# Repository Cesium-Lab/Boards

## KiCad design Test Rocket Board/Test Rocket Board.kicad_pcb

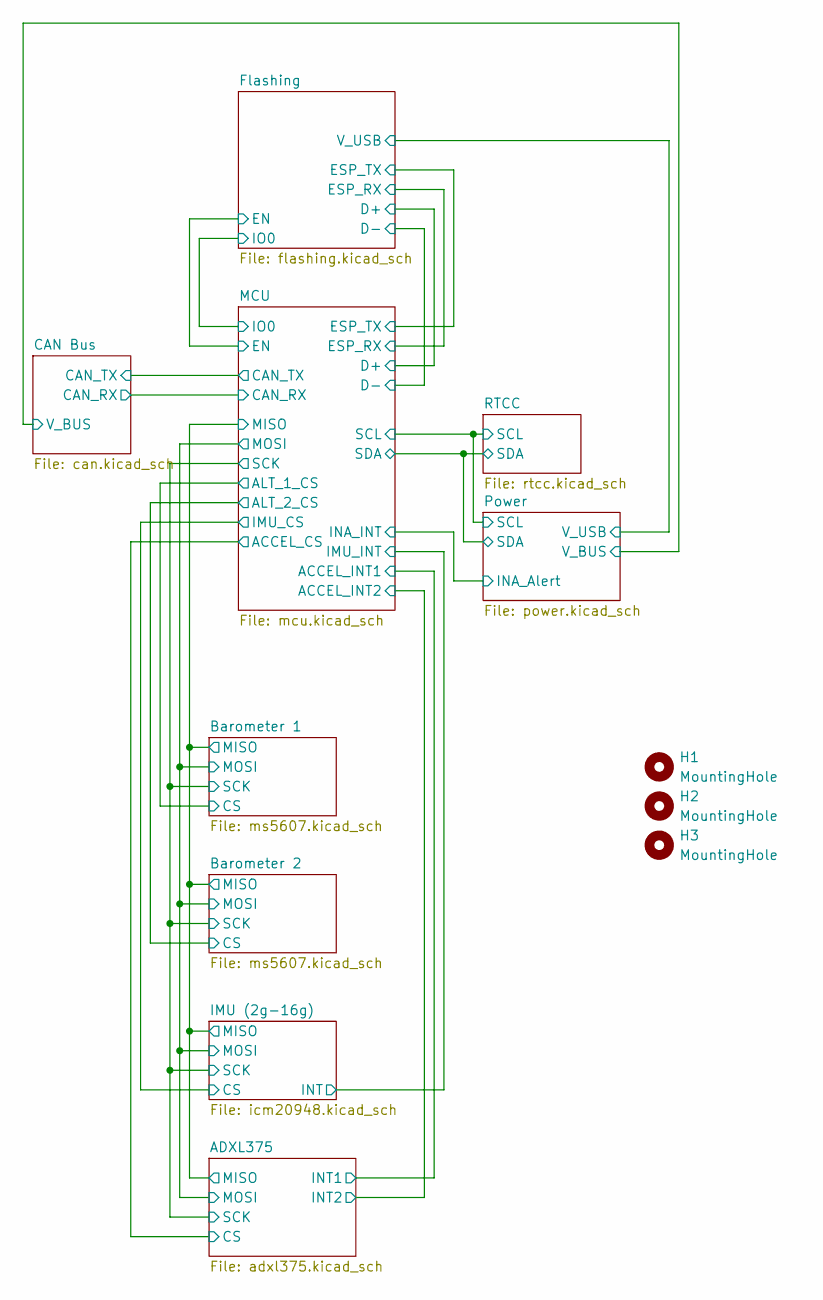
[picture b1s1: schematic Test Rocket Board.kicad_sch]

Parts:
H1, H2, H3: MountingHole; MountingHole_3.2mm_M3

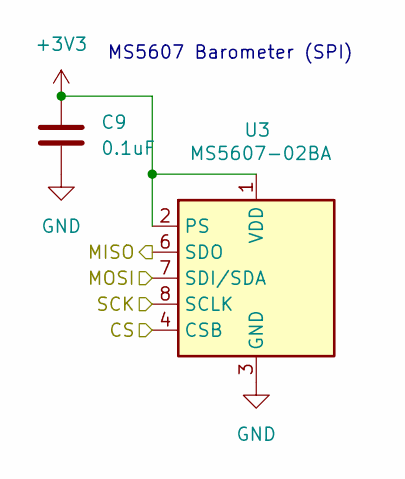
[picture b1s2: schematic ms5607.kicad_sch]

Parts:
C9: 0.1uF; C_0603_1608Metric
U3: MS5607-02BA; LGA-8_3x5mm_P1.25mm

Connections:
+3V3: C9.1, U3.1 (VDD), U3.2 (PS); also elsewhere on the board
/ADXL375/MISO: U3.6 (SDO); also elsewhere on the board
/ADXL375/MOSI: U3.7 (SDI/SDA); also elsewhere on the board
/ADXL375/SCK: U3.8 (SCLK); also elsewhere on the board
/Barometer 1/CS: U3.4 (CSB), U3.5 (CSB); also elsewhere on the board
GND: C9.2, U3.3 (GND); also elsewhere on the board

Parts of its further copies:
C10: 0.1uF; C_0603_1608Metric
U4: MS5607-02BA; LGA-8_3x5mm_P1.25mm

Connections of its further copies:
+3V3: C10.1, U4.1 (VDD), U4.2 (PS); also elsewhere on the board
/ADXL375/MISO: U4.6 (SDO); also elsewhere on the board
/ADXL375/MOSI: U4.7 (SDI/SDA); also elsewhere on the board
/ADXL375/SCK: U4.8 (SCLK); also elsewhere on the board
/Barometer 2/CS: U4.4 (CSB), U4.5 (CSB); also elsewhere on the board
GND: C10.2, U4.3 (GND); also elsewhere on the board

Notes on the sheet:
MS5607 Barometer (SPI)

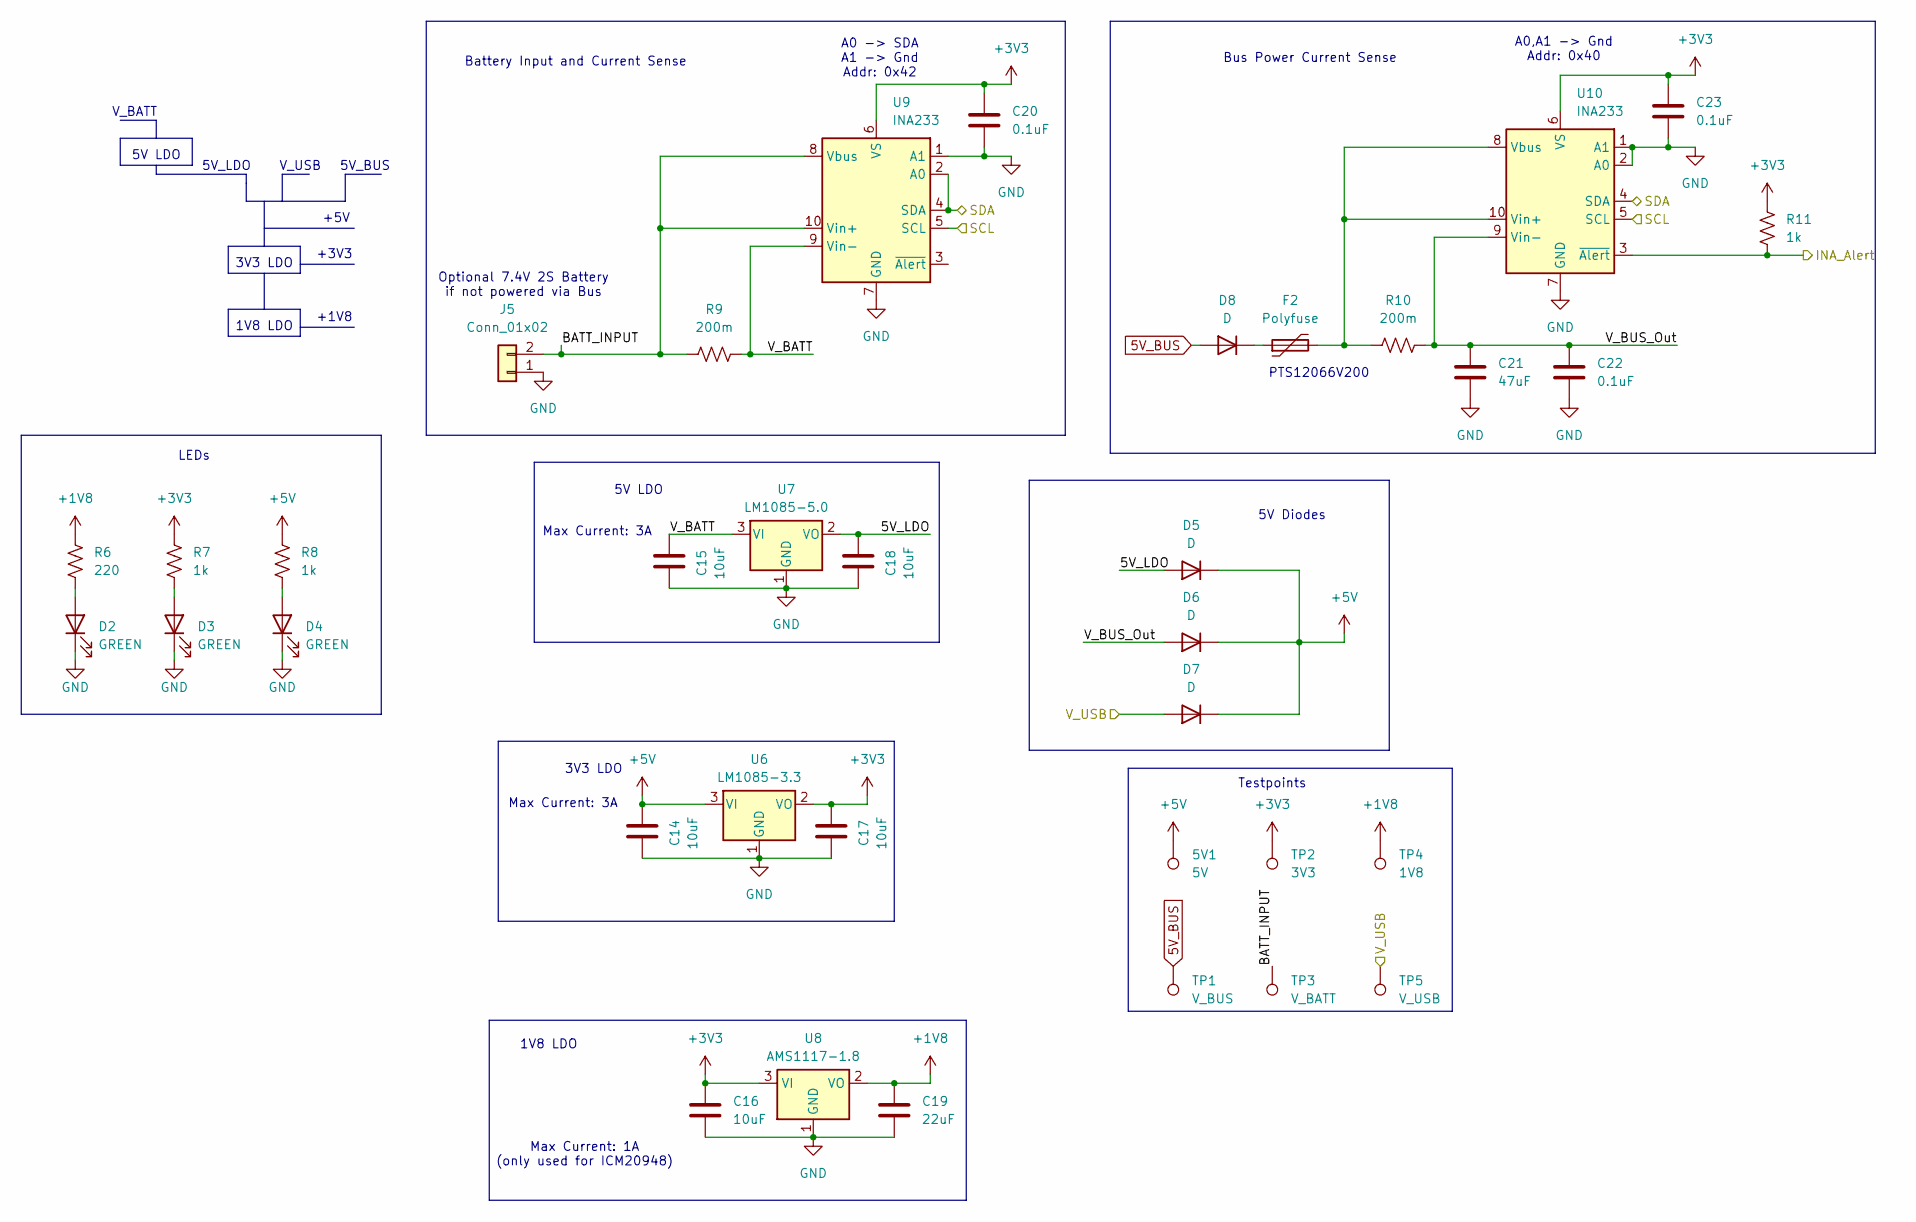
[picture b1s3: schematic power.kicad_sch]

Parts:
5V1: 5V; PinHeader_1x01_P2.54mm_Vertical
C14, C15, C16, C17, C18: 10uF; C_0603_1608Metric
C19: 22uF; C_0603_1608Metric
C20, C22, C23: 0.1uF; C_0603_1608Metric
C21: 47uF; C_0603_1608Metric
D2, D3, D4: GREEN; LED_0603_1608Metric_Pad1.05x0.95mm_HandSolder
D5, D6, D7, D8: D; D_0603_1608Metric
F2: Polyfuse; Fuse_1206_3216Metric
J5: Conn_01x02; AMASS_XT60-M_1x02_P7.20mm_Vertical
R6: 220; R_0603_1608Metric
R7, R8, R11: 1k; R_0603_1608Metric
R9, R10: 200m; R_0603_1608Metric
TP1: V_BUS; PinHeader_1x01_P2.54mm_Vertical
TP2: 3V3; PinHeader_1x01_P2.54mm_Vertical
TP3: V_BATT; PinHeader_1x01_P2.54mm_Vertical
TP4: 1V8; PinHeader_1x01_P2.54mm_Vertical
TP5: V_USB; PinHeader_1x01_P2.54mm_Vertical
U6: LM1085-3.3; TO-263-3_TabPin2
U7: LM1085-5.0; TO-263-3_TabPin2
U8: AMS1117-1.8; SOT-223-3_TabPin2
U9, U10: INA233; VSSOP-10_3x3mm_P0.5mm

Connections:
5V_BUS: D8.2 (A), TP1.1; also elsewhere on the board
+1V8: C19.1, R6.2, TP4.1, U8.2 (VO); also elsewhere on the board
+3V3: C16.1, C17.2, C20.1, C23.1, R7.2, R11.2, TP2.1, U6.2 (VO), U8.3 (VI), U9.6 (VS), U10.6 (VS); also elsewhere on the board
+5V: 5V1.1, C14.2, D5.1 (K), D6.1 (K), D7.1 (K), R8.2, U6.3 (VI); also elsewhere on the board
/Flashing/V_USB: D7.2 (A), TP5.1; also elsewhere on the board
/MCU/INA_INT: R11.1, U10.3 (~Alert); also elsewhere on the board
/MCU/SCL: U9.5 (SCL), U10.5 (SCL); also elsewhere on the board
/MCU/SDA: U9.2 (A0), U9.4 (SDA), U10.4 (SDA); also elsewhere on the board
/Power/5V_LDO: C18.2, D5.2 (A), U7.2 (VO)
/Power/BATT_INPUT: J5.2, R9.1, TP3.1, U9.8 (Vbus), U9.10 (Vin+)
/Power/V_BATT: C15.2, R9.2, U7.3 (VI), U9.9 (Vin-)
/Power/V_BUS_Out: C21.1, C22.1, D6.2 (A), R10.2, U10.9 (Vin-)
GND: C14.1, C15.1, C16.2, C17.1, C18.1, C19.2, C20.2, C21.2, C22.2, C23.2, D2.1 (K), D3.1 (K), D4.1 (K), J5.1, U6.1 (GND), U7.1 (GND), U8.1 (GND), U9.1 (A1), U9.7 (GND), U10.1 (A1), U10.2 (A0), U10.7 (GND); also elsewhere on the board
unnamed: D2.2 (A), R6.1
unnamed: D3.2 (A), R7.1
unnamed: D4.2 (A), R8.1
unnamed: D8.1 (K), F2.1
unnamed: F2.2, R10.1, U10.8 (Vbus), U10.10 (Vin+)

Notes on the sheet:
Battery Input and Current Sense
Testpoints
PTS12066V200
5V LDO
Max Current: 3A
LEDs
3V3 LDO
+3V3
Max Current: 1A (only used for ICM20948)
5V_LDO
1V8 LDO
Bus Power Current Sense
A0 -> SDA A1 -> Gnd Addr: 0x42
+1V8
+5V
5V_BUS
V_USB
Optional 7.4V 2S Battery if not powered via Bus
V_BATT
5V Diodes
A0,A1 -> Gnd Addr: 0x40

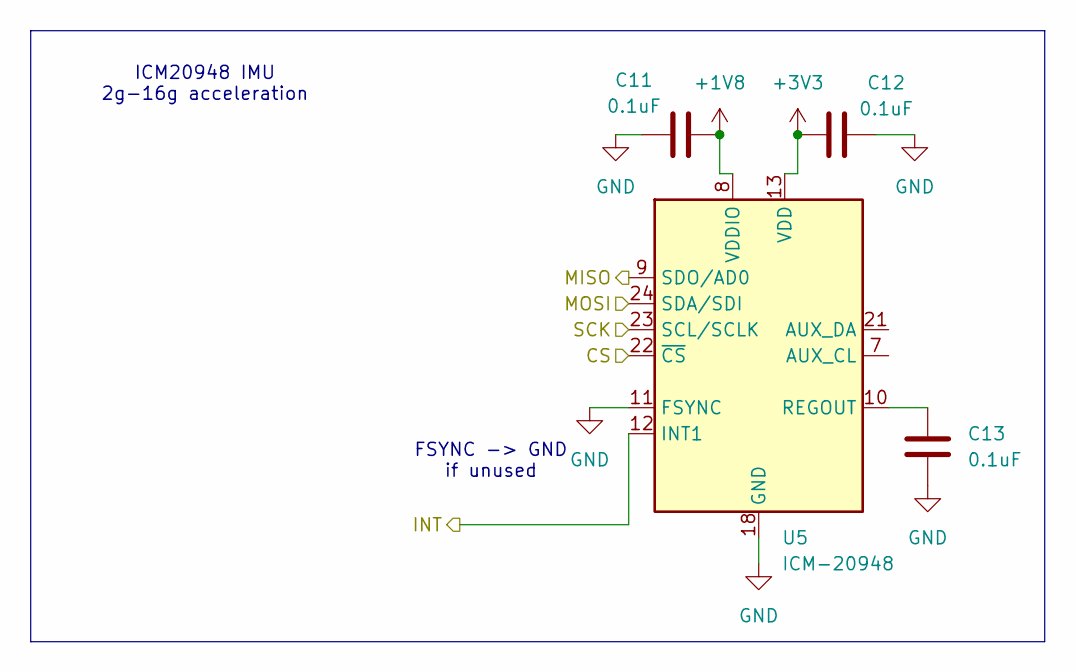
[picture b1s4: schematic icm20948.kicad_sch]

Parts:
C11, C12, C13: 0.1uF; C_0603_1608Metric
U5: ICM-20948; InvenSense_QFN-24_3x3mm_P0.4mm

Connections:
+1V8: C11.2, U5.8 (VDDIO); also elsewhere on the board
+3V3: C12.1, U5.13 (VDD); also elsewhere on the board
/ADXL375/MISO: U5.9 (SDO/AD0); also elsewhere on the board
/ADXL375/MOSI: U5.24 (SDA/SDI); also elsewhere on the board
/ADXL375/SCK: U5.23 (SCL/SCLK); also elsewhere on the board
/IMU (2g-16g)/CS: U5.22 (~CS); also elsewhere on the board
/IMU (2g-16g)/INT: U5.12 (INT1); also elsewhere on the board
GND: C11.1, C12.2, C13.2, U5.11 (FSYNC), U5.18 (GND), U5.20 (GND); also elsewhere on the board
unnamed: C13.1, U5.10 (REGOUT)

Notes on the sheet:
ICM20948 IMU 2g-16g acceleration
FSYNC -> GND if unused

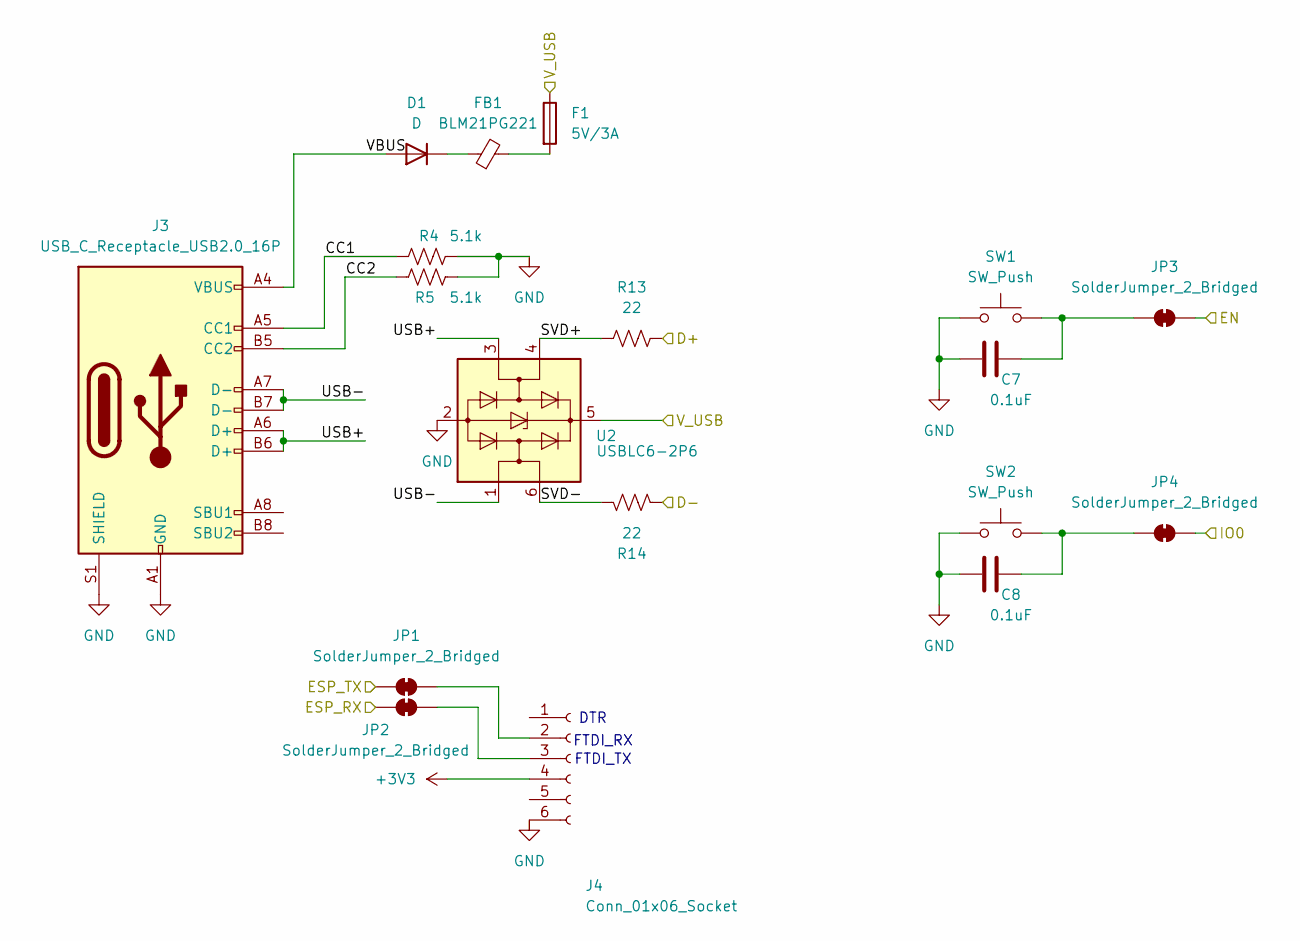
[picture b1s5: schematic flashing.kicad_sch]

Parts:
C7, C8: 0.1uF; C_0603_1608Metric
D1: D; D_0603_1608Metric
F1: 5V/3A; Fuse_0603_1608Metric
FB1: BLM21PG221; L_0603_1608Metric_Pad1.05x0.95mm_HandSolder
J3: USB_C_Receptacle_USB2.0_16P; USB_C_Receptacle_HRO_TYPE-C-31-M-12
J4: Conn_01x06_Socket; PinHeader_1x06_P2.54mm_Vertical
JP1, JP2, JP3, JP4: SolderJumper_2_Bridged; SolderJumper-2_P1.3mm_Bridged_Pad1.0x1.5mm
R4, R5: 5.1k; R_0603_1608Metric
R13, R14: 22; R_0603_1608Metric
SW1, SW2: SW_Push; SW_SPST_EVPBF
U2: USBLC6-2P6; SOT-666

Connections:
+3V3: J4.4; also elsewhere on the board
/Flashing/CC1: J3.A5 (CC1), R4.1
/Flashing/CC2: J3.B5 (CC2), R5.1
/Flashing/D+: R13.2; also elsewhere on the board
/Flashing/D-: R14.2; also elsewhere on the board
/Flashing/EN: JP3.2 (B); also elsewhere on the board
/Flashing/ESP_RX: JP2.2 (B); also elsewhere on the board
/Flashing/ESP_TX: JP1.1 (A); also elsewhere on the board
/Flashing/IO0: JP4.2 (B); also elsewhere on the board
/Flashing/SVD+: R13.1, U2.4 (I/O2)
/Flashing/SVD-: R14.1, U2.6 (I/O1)
/Flashing/USB+: J3.A6 (D+), J3.B6 (D+), U2.3 (I/O2)
/Flashing/USB-: J3.A7 (D-), J3.B7 (D-), U2.1 (I/O1)
/Flashing/VBUS: D1.2 (A), J3.A4 (VBUS), J3.A9 (VBUS), J3.B4 (VBUS), J3.B9 (VBUS)
/Flashing/V_USB: F1.1, U2.5 (VBUS); also elsewhere on the board
GND: C7.1, C8.1, J3.A1 (GND), J3.A12 (GND), J3.B1 (GND), J3.B12 (GND), J3.S1 (SHIELD), J4.6, R4.2, R5.2, SW1.1, SW2.1, U2.2 (GND); also elsewhere on the board
unnamed: D1.1 (K), FB1.1
unnamed: F1.2, FB1.2
unnamed: J4.2, JP1.2 (B)
unnamed: J4.3, JP2.1 (A)
unnamed: C7.2, JP3.1 (A), SW1.2
unnamed: C8.2, JP4.1 (A), SW2.2

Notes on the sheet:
DTR
FTDI_RX
FTDI_TX

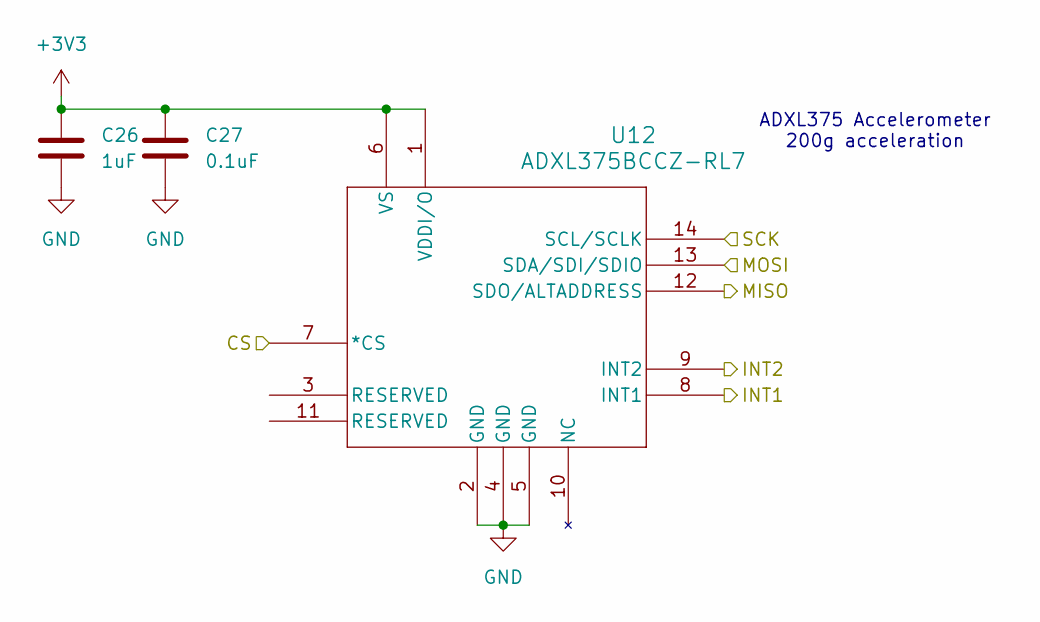
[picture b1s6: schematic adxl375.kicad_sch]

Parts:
C26: 1uF; C_0603_1608Metric
C27: 0.1uF; C_0603_1608Metric
U12: ADXL375BCCZ-RL7; LGA_CC-14-1_ADI

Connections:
+3V3: C26.1, C27.1, U12.1 (VDDI/O), U12.6 (VS); also elsewhere on the board
/ADXL375/CS: U12.7 (*CS); also elsewhere on the board
/ADXL375/INT1: U12.8 (INT1); also elsewhere on the board
/ADXL375/INT2: U12.9 (INT2); also elsewhere on the board
/ADXL375/MISO: U12.12 (SDO/ALTADDRESS); also elsewhere on the board
/ADXL375/MOSI: U12.13 (SDA/SDI/SDIO); also elsewhere on the board
/ADXL375/SCK: U12.14 (SCL/SCLK); also elsewhere on the board
GND: C26.2, C27.2, U12.2 (GND), U12.4 (GND), U12.5 (GND); also elsewhere on the board

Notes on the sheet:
ADXL375 Accelerometer 200g acceleration

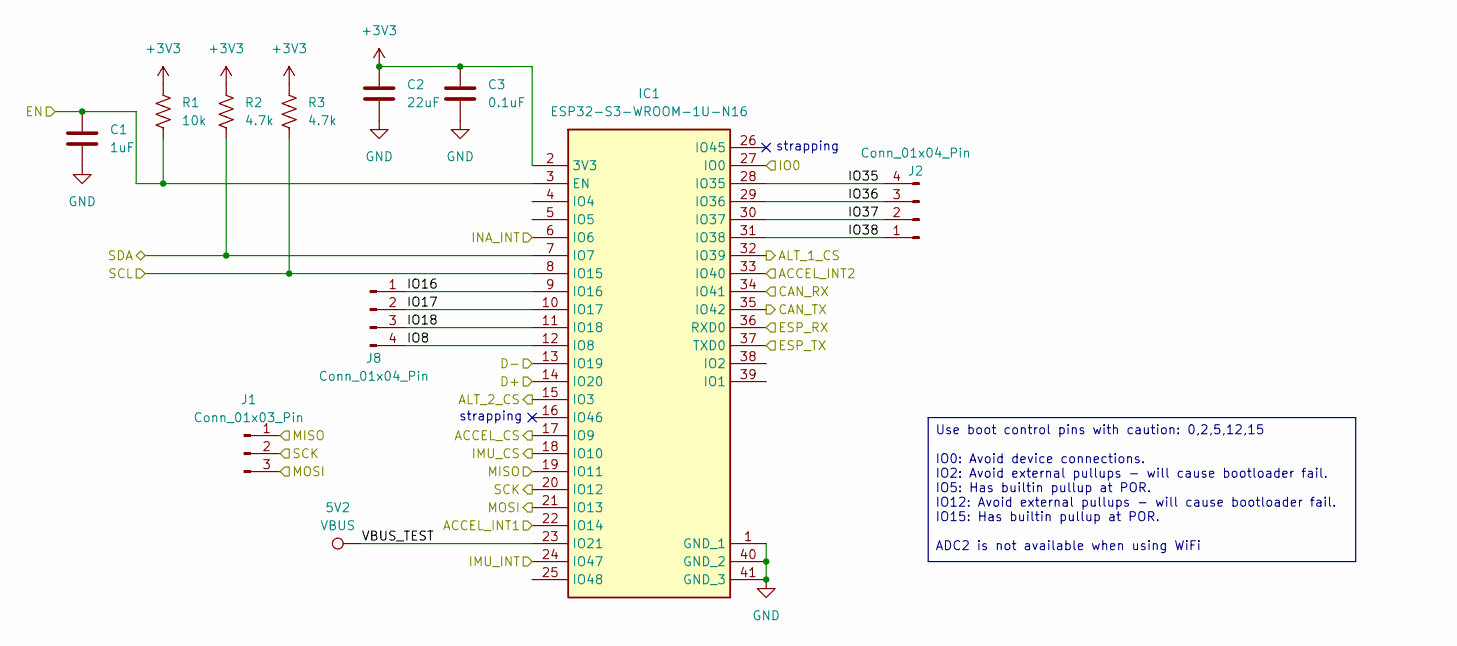
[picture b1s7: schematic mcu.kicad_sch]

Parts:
5V2: VBUS; PinHeader_1x01_P2.54mm_Vertical
C1: 1uF; C_0603_1608Metric
C2: 22uF; C_0603_1608Metric
C3: 0.1uF; C_0603_1608Metric
IC1: ESP32-S3-WROOM-1U-N16; ESP32-S3-WROOM-1U; Mouser Part Number 356-ESP32S3WROM1UN16
J1: Conn_01x03_Pin; PinHeader_1x03_P2.54mm_Vertical
J2, J8: Conn_01x04_Pin; PinHeader_1x04_P2.54mm_Vertical
R1: 10k; R_0603_1608Metric
R2, R3: 4.7k; R_0603_1608Metric

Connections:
+3V3: C2.2, C3.2, IC1.2 (3V3), R1.1, R2.1, R3.1; also elsewhere on the board
/ADXL375/CS: IC1.17 (IO9); also elsewhere on the board
/ADXL375/INT1: IC1.22 (IO14); also elsewhere on the board
/ADXL375/INT2: IC1.33 (IO40); also elsewhere on the board
/ADXL375/MISO: IC1.19 (IO11), J1.1; also elsewhere on the board
/ADXL375/MOSI: IC1.21 (IO13), J1.3; also elsewhere on the board
/ADXL375/SCK: IC1.20 (IO12), J1.2; also elsewhere on the board
/Barometer 1/CS: IC1.32 (IO39); also elsewhere on the board
/Barometer 2/CS: IC1.15 (IO3); also elsewhere on the board
/CAN Bus/CAN_RX: IC1.34 (IO41); also elsewhere on the board
/CAN Bus/CAN_TX: IC1.35 (IO42); also elsewhere on the board
/Flashing/D+: IC1.14 (IO20); also elsewhere on the board
/Flashing/D-: IC1.13 (IO19); also elsewhere on the board
/Flashing/EN: C1.2, IC1.3 (EN), R1.2; also elsewhere on the board
/Flashing/ESP_RX: IC1.36 (RXD0); also elsewhere on the board
/Flashing/ESP_TX: IC1.37 (TXD0); also elsewhere on the board
/Flashing/IO0: IC1.27 (IO0); also elsewhere on the board
/IMU (2g-16g)/CS: IC1.18 (IO10); also elsewhere on the board
/IMU (2g-16g)/INT: IC1.24 (IO47); also elsewhere on the board
/MCU/INA_INT: IC1.6 (IO6); also elsewhere on the board
/MCU/IO8: IC1.12 (IO8), J8.4
/MCU/IO16: IC1.9 (IO16), J8.1
/MCU/IO17: IC1.10 (IO17), J8.2
/MCU/IO18: IC1.11 (IO18), J8.3
/MCU/IO35: IC1.28 (IO35), J2.4
/MCU/IO36: IC1.29 (IO36), J2.3
/MCU/IO37: IC1.30 (IO37), J2.2
/MCU/IO38: IC1.31 (IO38), J2.1
/MCU/SCL: IC1.8 (IO15), R3.2; also elsewhere on the board
/MCU/SDA: IC1.7 (IO7), R2.2; also elsewhere on the board
/MCU/VBUS_TEST: 5V2.1, IC1.23 (IO21); also elsewhere on the board
GND: C1.1, C2.1, C3.1, IC1.1 (GND_1), IC1.40 (GND_2), IC1.41 (GND_3); also elsewhere on the board

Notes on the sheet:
strapping
Use boot control pins with caution: 0,2,5,12,15 IO0: Avoid device connections. IO2: Avoid external pullups - will cause bootloader fail. IO5: Has builtin pullup at POR. IO12: Avoid external pullups - will cause bootloader fail. IO15: Has builtin pullup at POR. ADC2 is not available when using WiFi

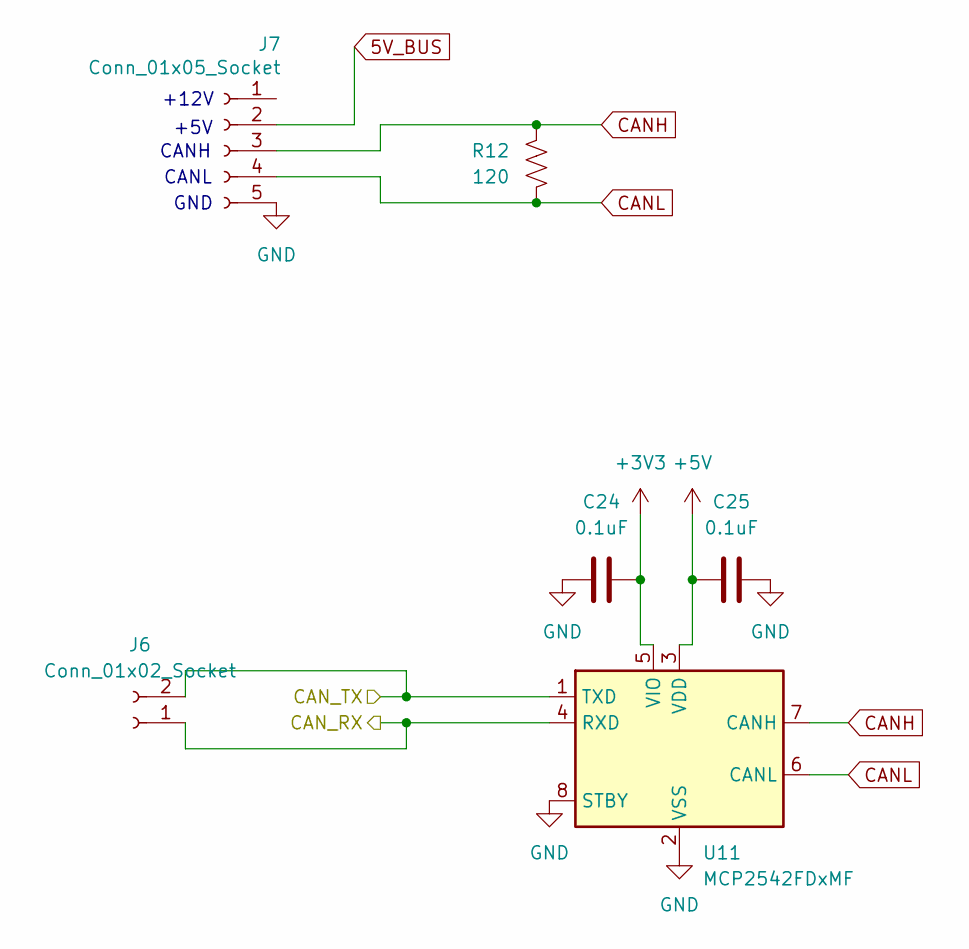
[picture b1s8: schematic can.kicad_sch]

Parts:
C24, C25: 0.1uF; C_0603_1608Metric
J6: Conn_01x02_Socket; PinHeader_1x02_P2.54mm_Vertical
J7: Conn_01x05_Socket; PinHeader_1x05_P2.54mm_Vertical
R12: 120; R_0603_1608Metric
U11: MCP2542FDxMF; DFN-8-1EP_3x3mm_P0.65mm_EP1.55x2.4mm

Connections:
5V_BUS: J7.2; also elsewhere on the board
+3V3: C24.2, U11.5 (VIO); also elsewhere on the board
+5V: C25.1, U11.3 (VDD); also elsewhere on the board
/CAN Bus/CAN_RX: J6.1, U11.4 (RXD); also elsewhere on the board
/CAN Bus/CAN_TX: J6.2, U11.1 (TXD); also elsewhere on the board
CANH: J7.3, R12.1, U11.7 (CANH)
CANL: J7.4, R12.2, U11.6 (CANL)
GND: C24.1, C25.2, J7.5, U11.2 (VSS), U11.8 (STBY), U11.9 (VSS); also elsewhere on the board

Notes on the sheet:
CANH
+5V
+12V
GND
CANL

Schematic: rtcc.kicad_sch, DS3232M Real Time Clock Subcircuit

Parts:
BT1: BAT-HLD-012-THM; BAT_BAT-HLD-012-THM
C4, C6: 0.1uF; C_0603_1608Metric
C5: 1uF; C_0603_1608Metric
U1: DS3232M; SOIC-8_3.9x4.9mm_P1.27mm

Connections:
+3V3: C5.1, C6.1, U1.2 (VCC); also elsewhere on the board
/MCU/SCL: U1.8 (SCL); also elsewhere on the board
/MCU/SDA: U1.7 (SDA); also elsewhere on the board
GND: BT1.N, C4.1, C5.2, C6.2, U1.5 (GND); also elsewhere on the board
unnamed: BT1.P1, C4.2, U1.6 (VBAT)

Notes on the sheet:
2.5µA timekeeping current -> 14,000 Hours
3V Backup Battery CR1220 (35 mAh)

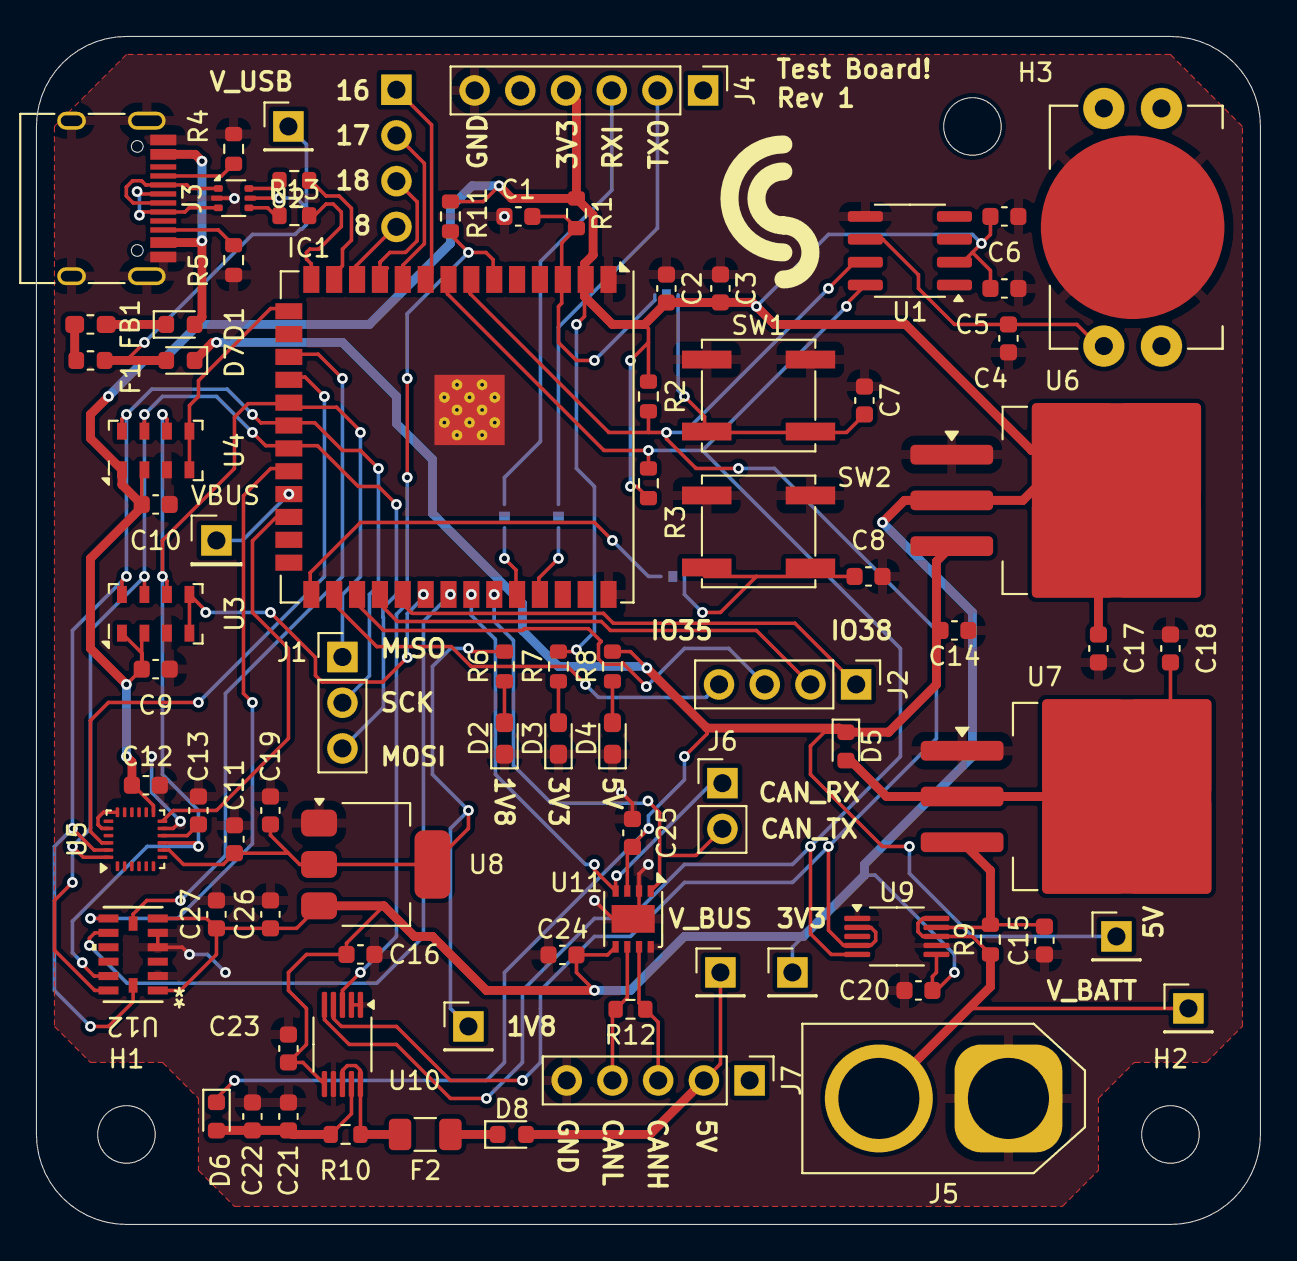
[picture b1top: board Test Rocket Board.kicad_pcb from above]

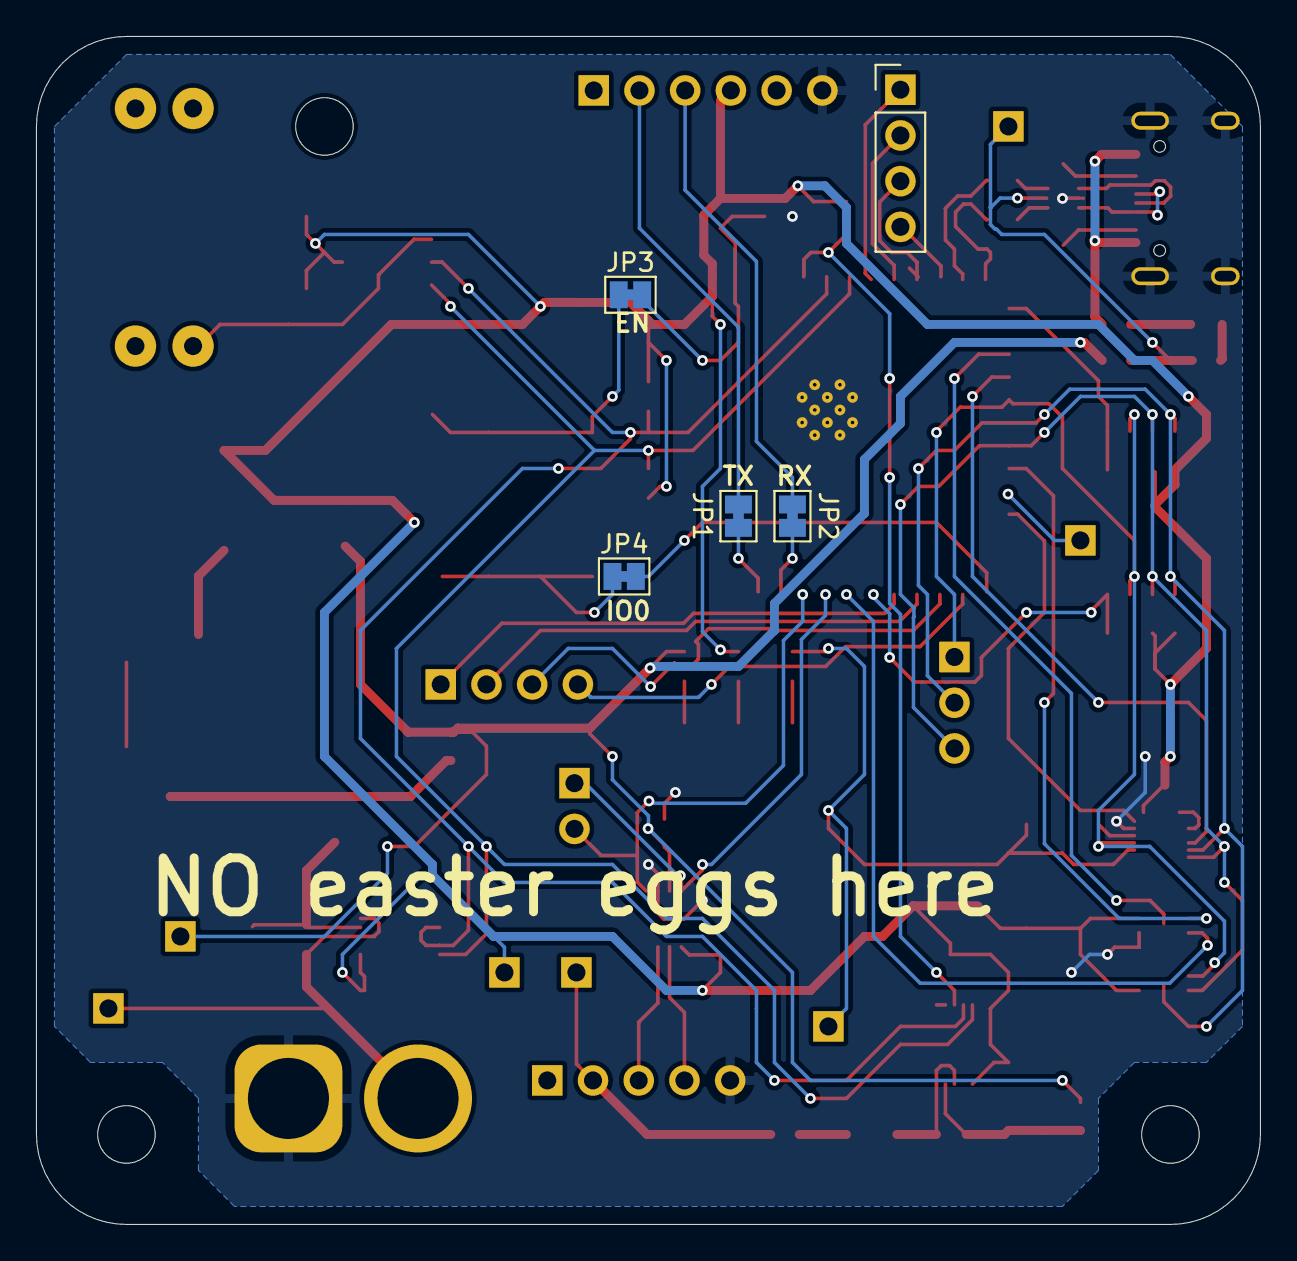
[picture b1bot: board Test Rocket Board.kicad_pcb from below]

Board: 2 copper layers, 68.0 x 66.0 mm, 90 parts (5 on the bottom side), 62 nets.

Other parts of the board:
VBUS: VBUS; PinHeader_1x01_P2.54mm_Vertical

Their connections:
/MCU/VBUS_TEST: VBUS.1; also elsewhere on the board

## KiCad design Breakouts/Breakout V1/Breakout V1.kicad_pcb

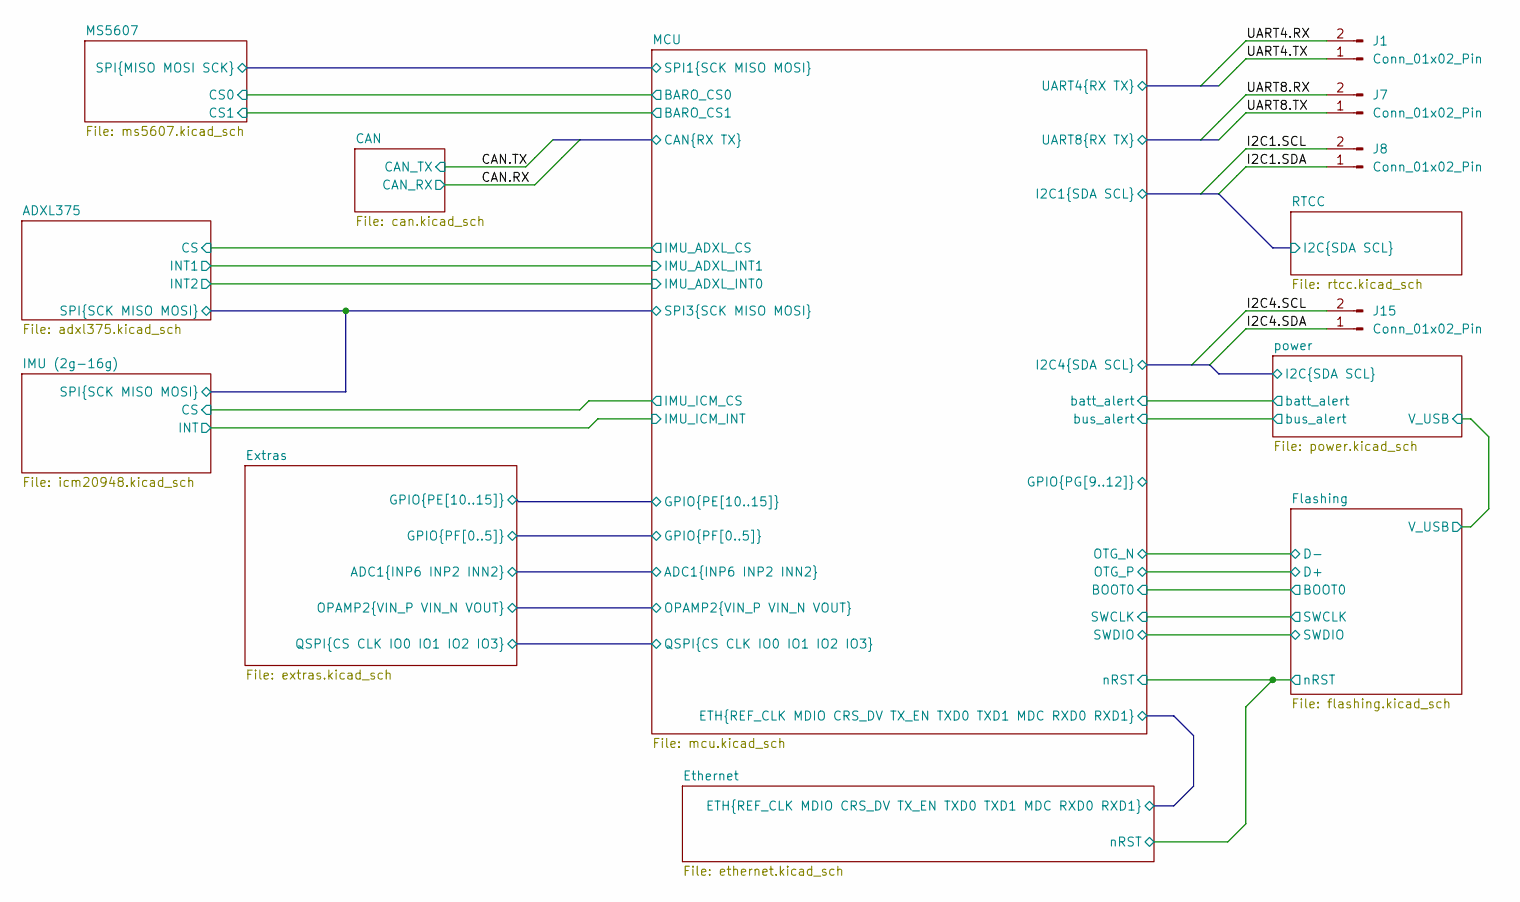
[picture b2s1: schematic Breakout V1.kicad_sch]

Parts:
J1, J7, J8, J15: Conn_01x02_Pin; PinHeader_1x02_P2.54mm_Vertical

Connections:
/MCU/I2C1.SCL: J8.2; also elsewhere on the board
/MCU/I2C1.SDA: J8.1; also elsewhere on the board
/MCU/I2C4.SCL: J15.2; also elsewhere on the board
/MCU/I2C4.SDA: J15.1; also elsewhere on the board
/MCU/UART4.RX: J1.2; also elsewhere on the board
/MCU/UART4.TX: J1.1; also elsewhere on the board
/MCU/UART8.RX: J7.2; also elsewhere on the board
/MCU/UART8.TX: J7.1; also elsewhere on the board
